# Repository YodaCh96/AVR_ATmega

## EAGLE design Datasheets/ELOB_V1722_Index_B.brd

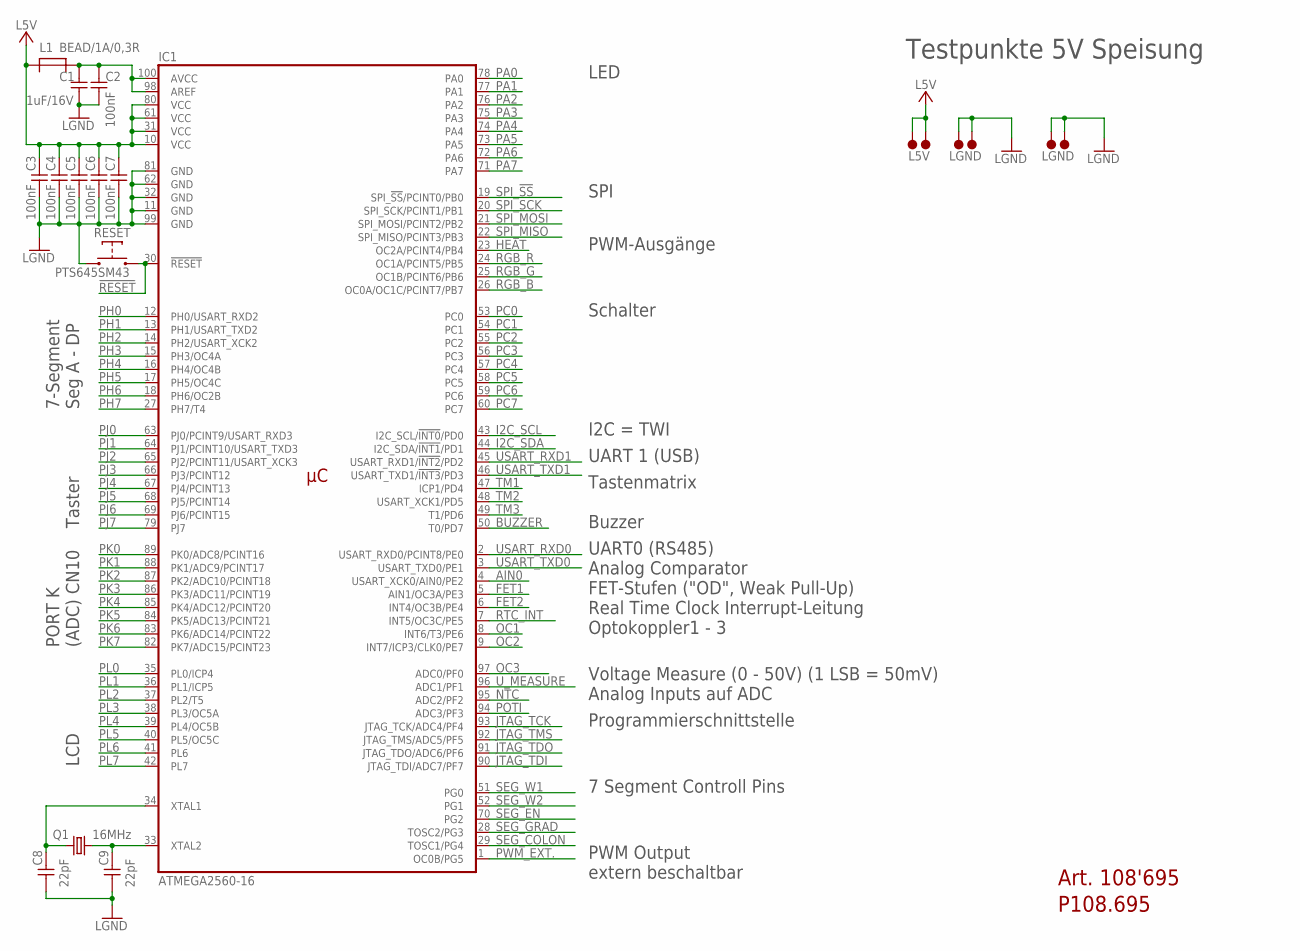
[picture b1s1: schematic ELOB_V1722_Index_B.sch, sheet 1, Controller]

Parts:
.L5V: L5V; TESTPAD_2P_V1_NORESTRICT
C1: 1uF/16V; C0603
C2, C3, C4, C5, C6, C7: 100nF; C0603
C8, C9: 22pF; C0603
IC1: ATMEGA2560-16; TQFP100
L1: BEAD/1A/0,3R; R1206
Q1: 16MHz; HC49_S
RESET: PTS645SM43; DTSM-6
TP1, TP12: LGND; TESTPAD_2P_V1_NORESTRICT

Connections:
!RESET!: IC1.30 (!RESET!), RESET.3 (2), RESET.4 (2); also elsewhere on the board
AIN0: IC1.4 (USART_XCK0/AIN0/PE2); also elsewhere on the board
BUZZER: IC1.50 (T0/PD7); also elsewhere on the board
FET1: IC1.5 (AIN1/OC3A/PE3); also elsewhere on the board
FET2: IC1.6 (INT4/OC3B/PE4); also elsewhere on the board
HEAT: IC1.23 (OC2A/PCINT4/PB4); also elsewhere on the board
I2C_SCL: IC1.43 (I2C_SCL/!INT0!/PD0); also elsewhere on the board
I2C_SDA: IC1.44 (I2C_SDA/!INT1!/PD1); also elsewhere on the board
JTAG_TCK: IC1.93 (JTAG_TCK/ADC4/PF4); also elsewhere on the board
JTAG_TDI: IC1.90 (JTAG_TDI/ADC7/PF7); also elsewhere on the board
JTAG_TDO: IC1.91 (JTAG_TDO/ADC6/PF6); also elsewhere on the board
JTAG_TMS: IC1.92 (JTAG_TMS/ADC5/PF5); also elsewhere on the board
L5V: .L5V.1, .L5V.2, C3.1, C4.1, C5.1, C6.1, C7.1, IC1.10 (VCC), IC1.31 (VCC), IC1.61 (VCC), IC1.80 (VCC), L1.1; also elsewhere on the board
LGND: C1.2, C2.2, C3.2, C4.2, C5.2, C6.2, C7.2, C8.2, C9.2, IC1.11 (GND), IC1.32 (GND), IC1.62 (GND), IC1.81 (GND), IC1.99 (GND), RESET.1, RESET.2 (1), TP1.1, TP1.2, TP12.1, TP12.2; also elsewhere on the board
unnamed: C8.1, IC1.34 (XTAL1), Q1.1
unnamed: C9.1, IC1.33 (XTAL2), Q1.2
unnamed: C1.1, C2.1, IC1.98 (AREF), IC1.100 (AVCC), L1.2
NTC: IC1.95 (ADC2/PF2); also elsewhere on the board
OC1: IC1.8 (INT6/T3/PE6); also elsewhere on the board
OC2: IC1.9 (INT7/ICP3/CLK0/PE7); also elsewhere on the board
OC3: IC1.97 (ADC0/PF0); also elsewhere on the board
PA0: IC1.78 (PA0); also elsewhere on the board
PA1: IC1.77 (PA1); also elsewhere on the board
PA2: IC1.76 (PA2); also elsewhere on the board
PA3: IC1.75 (PA3); also elsewhere on the board
PA4: IC1.74 (PA4); also elsewhere on the board
PA5: IC1.73 (PA5); also elsewhere on the board
PA6: IC1.72 (PA6); also elsewhere on the board
PA7: IC1.71 (PA7); also elsewhere on the board
PC0: IC1.53 (PC0); also elsewhere on the board
PC1: IC1.54 (PC1); also elsewhere on the board
PC2: IC1.55 (PC2); also elsewhere on the board
PC3: IC1.56 (PC3); also elsewhere on the board
PC4: IC1.57 (PC4); also elsewhere on the board
PC5: IC1.58 (PC5); also elsewhere on the board
PC6: IC1.59 (PC6); also elsewhere on the board
PC7: IC1.60 (PC7); also elsewhere on the board
PH0: IC1.12 (PH0/USART_RXD2); also elsewhere on the board
PH1: IC1.13 (PH1/USART_TXD2); also elsewhere on the board
PH2: IC1.14 (PH2/USART_XCK2); also elsewhere on the board
PH3: IC1.15 (PH3/OC4A); also elsewhere on the board
PH4: IC1.16 (PH4/OC4B); also elsewhere on the board
PH5: IC1.17 (PH5/OC4C); also elsewhere on the board
PH6: IC1.18 (PH6/OC2B); also elsewhere on the board
PH7: IC1.27 (PH7/T4); also elsewhere on the board
PJ0: IC1.63 (PJ0/PCINT9/USART_RXD3); also elsewhere on the board
PJ1: IC1.64 (PJ1/PCINT10/USART_TXD3); also elsewhere on the board
PJ2: IC1.65 (PJ2/PCINT11/USART_XCK3); also elsewhere on the board
PJ3: IC1.66 (PJ3/PCINT12); also elsewhere on the board
PJ4: IC1.67 (PJ4/PCINT13); also elsewhere on the board
PJ5: IC1.68 (PJ5/PCINT14); also elsewhere on the board
PJ6: IC1.69 (PJ6/PCINT15); also elsewhere on the board
PJ7: IC1.79 (PJ7); also elsewhere on the board
PK0: IC1.89 (PK0/ADC8/PCINT16); also elsewhere on the board
PK1: IC1.88 (PK1/ADC9/PCINT17); also elsewhere on the board
PK2: IC1.87 (PK2/ADC10/PCINT18); also elsewhere on the board
PK3: IC1.86 (PK3/ADC11/PCINT19); also elsewhere on the board
PK4: IC1.85 (PK4/ADC12/PCINT20); also elsewhere on the board
PK5: IC1.84 (PK5/ADC13/PCINT21); also elsewhere on the board
PK6: IC1.83 (PK6/ADC14/PCINT22); also elsewhere on the board
PK7: IC1.82 (PK7/ADC15/PCINT23); also elsewhere on the board
PL0: IC1.35 (PL0/ICP4); also elsewhere on the board
PL1: IC1.36 (PL1/ICP5); also elsewhere on the board
PL2: IC1.37 (PL2/T5); also elsewhere on the board
PL3: IC1.38 (PL3/OC5A); also elsewhere on the board
PL4: IC1.39 (PL4/OC5B); also elsewhere on the board
PL5: IC1.40 (PL5/OC5C); also elsewhere on the board
PL6: IC1.41 (PL6); also elsewhere on the board
PL7: IC1.42 (PL7); also elsewhere on the board
POTI: IC1.94 (ADC3/PF3); also elsewhere on the board
PWM_EXT.: IC1.1 (OC0B/PG5); also elsewhere on the board
RGB_B: IC1.26 (OC0A/OC1C/PCINT7/PB7); also elsewhere on the board
RGB_G: IC1.25 (OC1B/PCINT6/PB6); also elsewhere on the board
RGB_R: IC1.24 (OC1A/PCINT5/PB5); also elsewhere on the board
RTC_INT: IC1.7 (INT5/OC3C/PE5); also elsewhere on the board
SEG_COLON: IC1.29 (TOSC1/PG4); also elsewhere on the board
SEG_EN: IC1.70 (PG2); also elsewhere on the board
SEG_GRAD: IC1.28 (TOSC2/PG3); also elsewhere on the board
SEG_W1: IC1.51 (PG0); also elsewhere on the board
SEG_W2: IC1.52 (PG1); also elsewhere on the board
SPI_!SS!: IC1.19 (SPI_!SS!/PCINT0/PB0); also elsewhere on the board
SPI_MISO: IC1.22 (SPI_MISO/PCINT3/PB3); also elsewhere on the board
SPI_MOSI: IC1.21 (SPI_MOSI/PCINT2/PB2); also elsewhere on the board
SPI_SCK: IC1.20 (SPI_SCK/PCINT1/PB1); also elsewhere on the board
TM1: IC1.47 (ICP1/PD4); also elsewhere on the board
TM2: IC1.48 (USART_XCK1/PD5); also elsewhere on the board
TM3: IC1.49 (T1/PD6); also elsewhere on the board
USART_RXD0: IC1.2 (USART_RXD0/PCINT8/PE0); also elsewhere on the board
USART_RXD1: IC1.45 (USART_RXD1/!INT2!/PD2); also elsewhere on the board
USART_TXD0: IC1.3 (USART_TXD0/PE1); also elsewhere on the board
USART_TXD1: IC1.46 (USART_TXD1/!INT3!/PD3); also elsewhere on the board
U_MEASURE: IC1.96 (ADC1/PF1); also elsewhere on the board

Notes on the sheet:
7-Segment
PORT K (ADC) CN10
Taster
LCD
Tastenmatrix
Art. 108'695
P108.695
7 Segment Controll Pins
PWM Output
Programmierschnittstelle
Analog Inputs auf ADC
Optokoppler1 - 3
Real Time Clock Interrupt-Leitung
FET-Stufen ("OD", Weak Pull-Up)
Analog Comparator
UART0 (RS485)
UART 1 (USB)
I2C = TWI
Schalter
SPI
LED
PWM-Ausgänge
Seg A - DP
extern beschaltbar
Buzzer
Voltage Measure (0 - 50V) (1 LSB = 50mV)
Testpunkte 5V Speisung

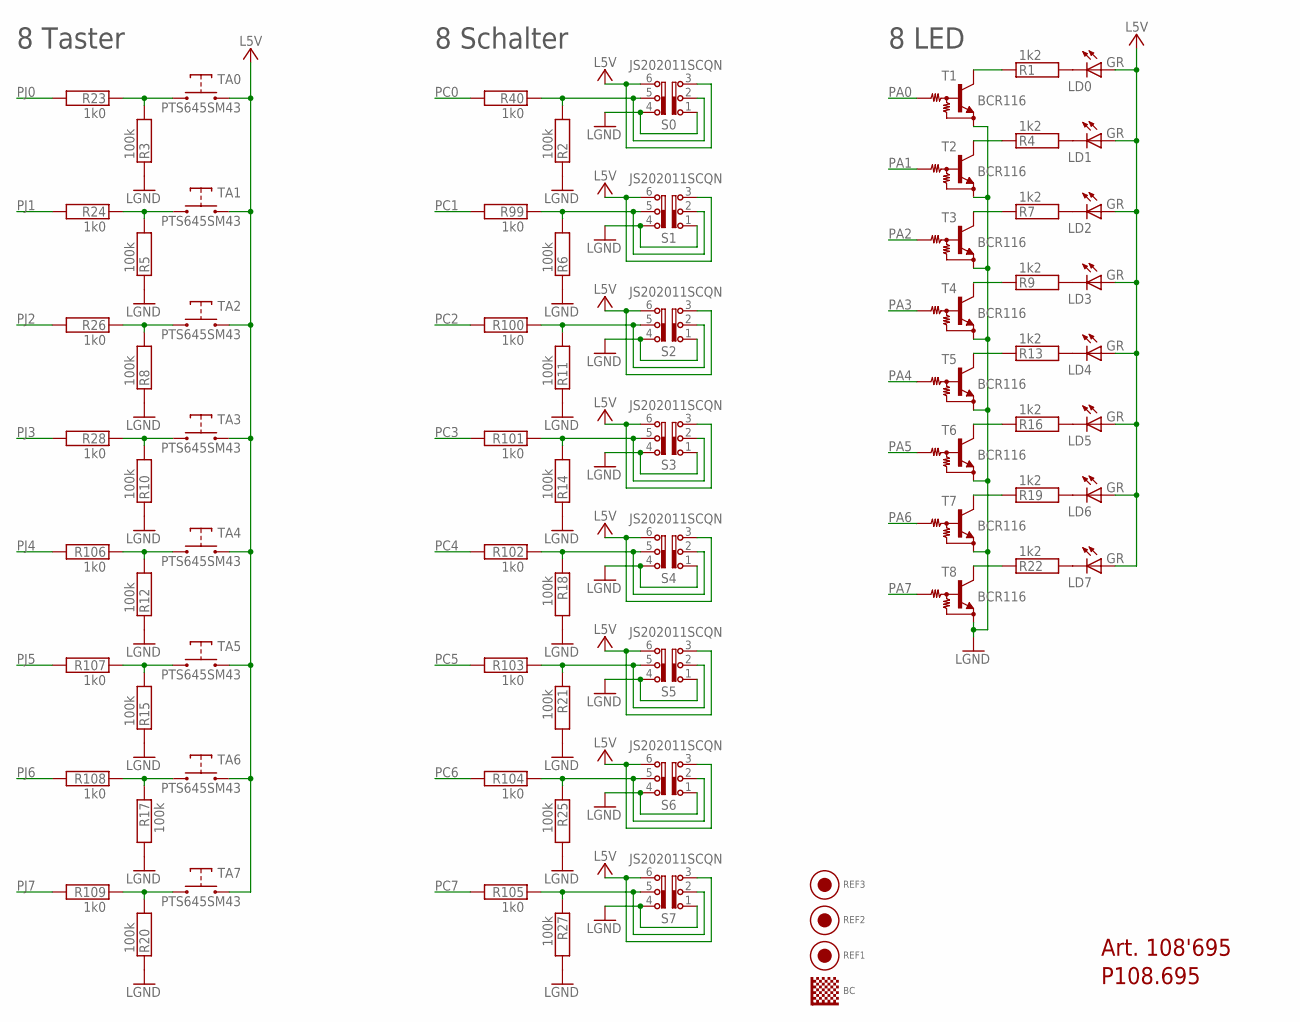
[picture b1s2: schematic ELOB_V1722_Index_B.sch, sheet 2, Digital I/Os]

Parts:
BC: BC; BARCODE
LD0, LD1, LD2, LD3, LD4, LD5, LD6, LD7: GR; LED_0805
R1, R4, R7, R9, R13, R16, R19, R22: 1k2; R0603
R2, R3, R5, R6, R8, R10, R11, R12, R14, R15, R17, R18, R20, R21, R25, R27: 100k; R0603
R23, R24, R26, R28, R40, R99, R100, R101, R102, R103, R104, R105, R106, R107, R108, R109: 1k0; R0603
REF1, REF2, REF3: DOT; PAS_PLACE
S0, S1, S2, S3, S4, S5, S6, S7: JS202011SCQN
T1, T2, T3, T4, T5, T6, T7, T8: BCR116; SOT_23
TA0, TA1, TA2, TA3, TA4, TA5, TA6, TA7: PTS645SM43; DTSM-6

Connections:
L5V: LD0.A, LD1.A, LD2.A, LD3.A, LD4.A, LD5.A, LD6.A, LD7.A, S0.3, S0.6, S1.3, S1.6, S2.3, S2.6, S3.3, S3.6, S4.3, S4.6, S5.3, S5.6, S6.3, S6.6, S7.3, S7.6, TA0.1, TA0.2 (1), TA1.1, TA1.2 (1), TA2.1, TA2.2 (1), TA3.1, TA3.2 (1), TA4.1, TA4.2 (1), TA5.1, TA5.2 (1), TA6.1, TA6.2 (1), TA7.1, TA7.2 (1); also elsewhere on the board
LGND: R2.1, R3.1, R5.1, R6.1, R8.1, R10.1, R11.1, R12.1, R14.1, R15.1, R17.2, R18.2, R20.1, R21.2, R25.2, R27.2, S0.1, S0.4, S1.1, S1.4, S2.1, S2.4, S3.1, S3.4, S4.1, S4.4, S5.1, S5.4, S6.1, S6.4, S7.1, S7.4, T1.2 (E), T2.2 (E), T3.2 (E), T4.2 (E), T5.2 (E), T6.2 (E), T7.2 (E), T8.2 (E); also elsewhere on the board
unnamed: R1.1, T1.3 (C)
unnamed: LD1.K (C), R4.2
unnamed: LD0.K (C), R1.2
unnamed: LD2.K (C), R7.2
unnamed: LD3.K (C), R9.2
unnamed: LD4.K (C), R13.2
unnamed: LD5.K (C), R16.2
unnamed: LD6.K (C), R19.2
unnamed: LD7.K (C), R22.2
unnamed: R4.1, T2.3 (C)
unnamed: R7.1, T3.3 (C)
unnamed: R9.1, T4.3 (C)
unnamed: R13.1, T5.3 (C)
unnamed: R16.1, T6.3 (C)
unnamed: R19.1, T7.3 (C)
unnamed: R22.1, T8.3 (C)
unnamed: R2.2, R40.1, S0.2, S0.5
unnamed: R20.2, R109.1, TA7.3 (2), TA7.4 (2)
unnamed: R27.1, R105.1, S7.2, S7.5
unnamed: R17.1, R108.1, TA6.3 (2), TA6.4 (2)
unnamed: R15.2, R107.1, TA5.3 (2), TA5.4 (2)
unnamed: R12.2, R106.1, TA4.3 (2), TA4.4 (2)
unnamed: R25.1, R104.1, S6.2, S6.5
unnamed: R10.2, R28.1, TA3.3 (2), TA3.4 (2)
unnamed: R6.2, R99.1, S1.2, S1.5
unnamed: R8.2, R26.1, TA2.3 (2), TA2.4 (2)
unnamed: R21.1, R103.1, S5.2, S5.5
unnamed: R18.1, R102.1, S4.2, S4.5
unnamed: R14.2, R101.1, S3.2, S3.5
unnamed: R11.2, R100.1, S2.2, S2.5
unnamed: R5.2, R24.1, TA1.3 (2), TA1.4 (2)
unnamed: R3.2, R23.1, TA0.3 (2), TA0.4 (2)
PA0: T1.1 (B); also elsewhere on the board
PA1: T2.1 (B); also elsewhere on the board
PA2: T3.1 (B); also elsewhere on the board
PA3: T4.1 (B); also elsewhere on the board
PA4: T5.1 (B); also elsewhere on the board
PA5: T6.1 (B); also elsewhere on the board
PA6: T7.1 (B); also elsewhere on the board
PA7: T8.1 (B); also elsewhere on the board
PC0: R40.2; also elsewhere on the board
PC1: R99.2; also elsewhere on the board
PC2: R100.2; also elsewhere on the board
PC3: R101.2; also elsewhere on the board
PC4: R102.2; also elsewhere on the board
PC5: R103.2; also elsewhere on the board
PC6: R104.2; also elsewhere on the board
PC7: R105.2; also elsewhere on the board
PJ0: R23.2; also elsewhere on the board
PJ1: R24.2; also elsewhere on the board
PJ2: R26.2; also elsewhere on the board
PJ3: R28.2; also elsewhere on the board
PJ4: R106.2; also elsewhere on the board
PJ5: R107.2; also elsewhere on the board
PJ6: R108.2; also elsewhere on the board
PJ7: R109.2; also elsewhere on the board

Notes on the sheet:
Art. 108'695
P108.695
8 Taster
8 Schalter
8 LED

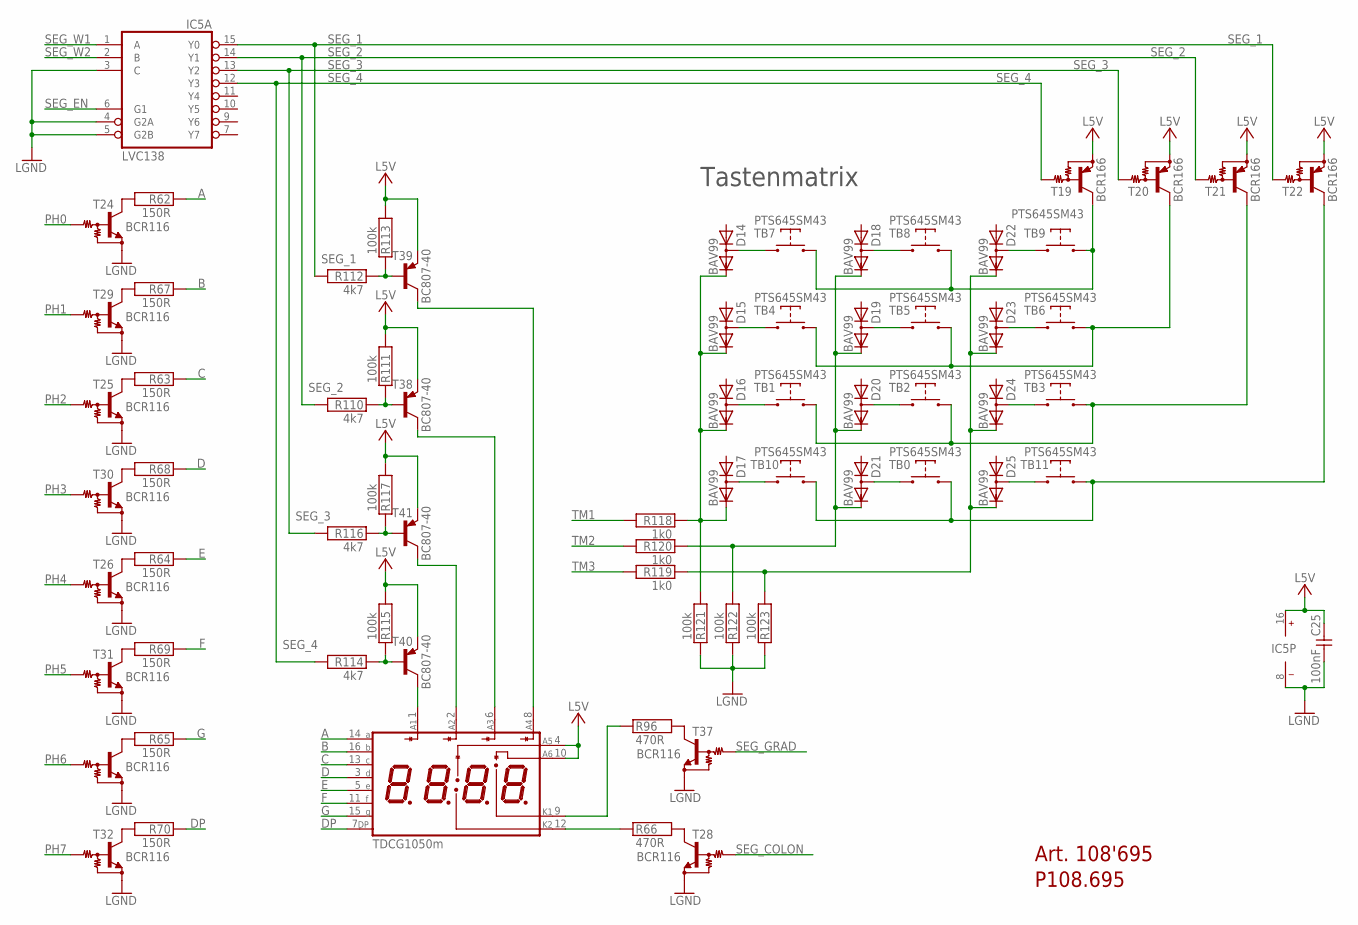
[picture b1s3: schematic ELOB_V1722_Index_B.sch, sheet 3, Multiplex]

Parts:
C25: 100nF; C0603
D14, D15, D16, D17, D18, D19, D20, D21, D22, D23, D24, D25: BAV99; SOT_23
IC5: LVC138; TSSOP_16
R62, R63, R64, R65, R67, R68, R69, R70: 150R; R0603
R66, R96: 470R; R0603
R110, R112, R114, R116: 4k7; R0603
R111, R113, R115, R117, R121, R122, R123: 100k; R0603
R118, R119, R120: 1k0; R0603
SEG1: TDCG1050m; 4-FACH_7-SEGMENT
T19, T20, T21, T22: BCR166; SOT_23
T24, T25, T26, T27, T28, T29, T30, T31, T32, T37: BCR116; SOT_23
T38, T39, T40, T41: BC807-40; SOT23
TB0, TB1, TB2, TB3, TB4, TB5, TB6, TB7, TB8, TB9, TB10, TB11: PTS645SM43; DTSM-6

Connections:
A: R62.1, SEG1.14 (A)
B: R67.1, SEG1.16 (B)
C: R63.1, SEG1.13 (C)
D: R68.1, SEG1.3 (D)
DP: R70.1, SEG1.7 (DP)
E: R64.1, SEG1.5 (E)
F: R69.1, SEG1.11 (F)
G: R65.1, SEG1.15 (G)
L5V: C25.1, IC5.16 (VCC), R111.2, R113.2, R115.2, R117.2, SEG1.4 (A), SEG1.10 (A), T19.2 (E), T20.2 (E), T21.2 (E), T22.2 (E), T38.2 (E), T39.2 (E), T40.2 (E), T41.2 (E); also elsewhere on the board
LGND: C25.2, IC5.3 (C), IC5.4 (G2A), IC5.5 (G2B), IC5.8 (GND), R121.1, R122.1, R123.1, T24.2 (E), T25.2 (E), T26.2 (E), T27.2 (E), T28.2 (E), T29.2 (E), T30.2 (E), T31.2 (E), T32.2 (E), T37.2 (E); also elsewhere on the board
unnamed: T19.3 (C), TB7.3 (2), TB7.4 (2), TB8.3 (2), TB8.4 (2), TB9.3 (2), TB9.4 (2)
unnamed: R66.2, T28.3 (C)
unnamed: R66.1, SEG1.12 (K2)
unnamed: R62.2, T24.3 (C)
unnamed: R67.2, T29.3 (C)
unnamed: T22.3 (C), TB0.3 (2), TB0.4 (2), TB10.3 (2), TB10.4 (2), TB11.3 (2), TB11.4 (2)
unnamed: T21.3 (C), TB1.3 (2), TB1.4 (2), TB2.3 (2), TB2.4 (2), TB3.3 (2), TB3.4 (2)
unnamed: D14.3 (AC), TB7.1, TB7.2 (1)
unnamed: R63.2, T25.3 (C)
unnamed: R68.2, T30.3 (C)
unnamed: R64.2, T26.3 (C)
unnamed: R69.2, T31.3 (C)
unnamed: R65.2, T27.3 (C)
unnamed: R70.2, T32.3 (C)
unnamed: R96.2, T37.3 (C)
unnamed: R96.1, SEG1.9 (K1)
unnamed: R110.1, R111.1, T38.1 (B)
unnamed: R114.1, R115.1, T40.1 (B)
unnamed: R112.1, R113.1, T39.1 (B)
unnamed: R116.1, R117.1, T41.1 (B)
unnamed: SEG1.1 (A), T40.3 (C)
unnamed: SEG1.2 (A), T41.3 (C)
unnamed: SEG1.6 (A), T38.3 (C)
unnamed: SEG1.8 (A), T39.3 (C)
unnamed: D15.3 (AC), TB4.1, TB4.2 (1)
unnamed: T20.3 (C), TB4.3 (2), TB4.4 (2), TB5.3 (2), TB5.4 (2), TB6.3 (2), TB6.4 (2)
unnamed: D16.3 (AC), TB1.1, TB1.2 (1)
unnamed: D17.3 (AC), TB10.1, TB10.2 (1)
unnamed: D22.2 (C), D23.2 (C), D24.2 (C), D25.2 (C), R119.1, R123.2
unnamed: D25.3 (AC), TB11.1, TB11.2 (1)
unnamed: D14.2 (C), D15.2 (C), D16.2 (C), D17.2 (C), R118.1, R121.2
unnamed: D18.3 (AC), TB8.1, TB8.2 (1)
unnamed: D19.3 (AC), TB5.1, TB5.2 (1)
unnamed: D20.3 (AC), TB2.1, TB2.2 (1)
unnamed: D21.3 (AC), TB0.1, TB0.2 (1)
unnamed: D18.2 (C), D19.2 (C), D20.2 (C), D21.2 (C), R120.1, R122.2
unnamed: D22.3 (AC), TB9.1, TB9.2 (1)
unnamed: D23.3 (AC), TB6.1, TB6.2 (1)
unnamed: D24.3 (AC), TB3.1, TB3.2 (1)
PH0: T24.1 (B); also elsewhere on the board
PH1: T29.1 (B); also elsewhere on the board
PH2: T25.1 (B); also elsewhere on the board
PH3: T30.1 (B); also elsewhere on the board
PH4: T26.1 (B); also elsewhere on the board
PH5: T31.1 (B); also elsewhere on the board
PH6: T27.1 (B); also elsewhere on the board
PH7: T32.1 (B); also elsewhere on the board
SEG_1: IC5.15 (Y0), R112.2, T22.1 (B)
SEG_2: IC5.14 (Y1), R110.2, T21.1 (B)
SEG_3: IC5.13 (Y2), R116.2, T20.1 (B)
SEG_4: IC5.12 (Y3), R114.2, T19.1 (B)
SEG_COLON: T28.1 (B); also elsewhere on the board
SEG_EN: IC5.6 (G1); also elsewhere on the board
SEG_GRAD: T37.1 (B); also elsewhere on the board
SEG_W1: IC5.1 (A); also elsewhere on the board
SEG_W2: IC5.2 (B); also elsewhere on the board
TM1: R118.2; also elsewhere on the board
TM2: R120.2; also elsewhere on the board
TM3: R119.2; also elsewhere on the board

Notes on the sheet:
Art. 108'695
P108.695
Tastenmatrix

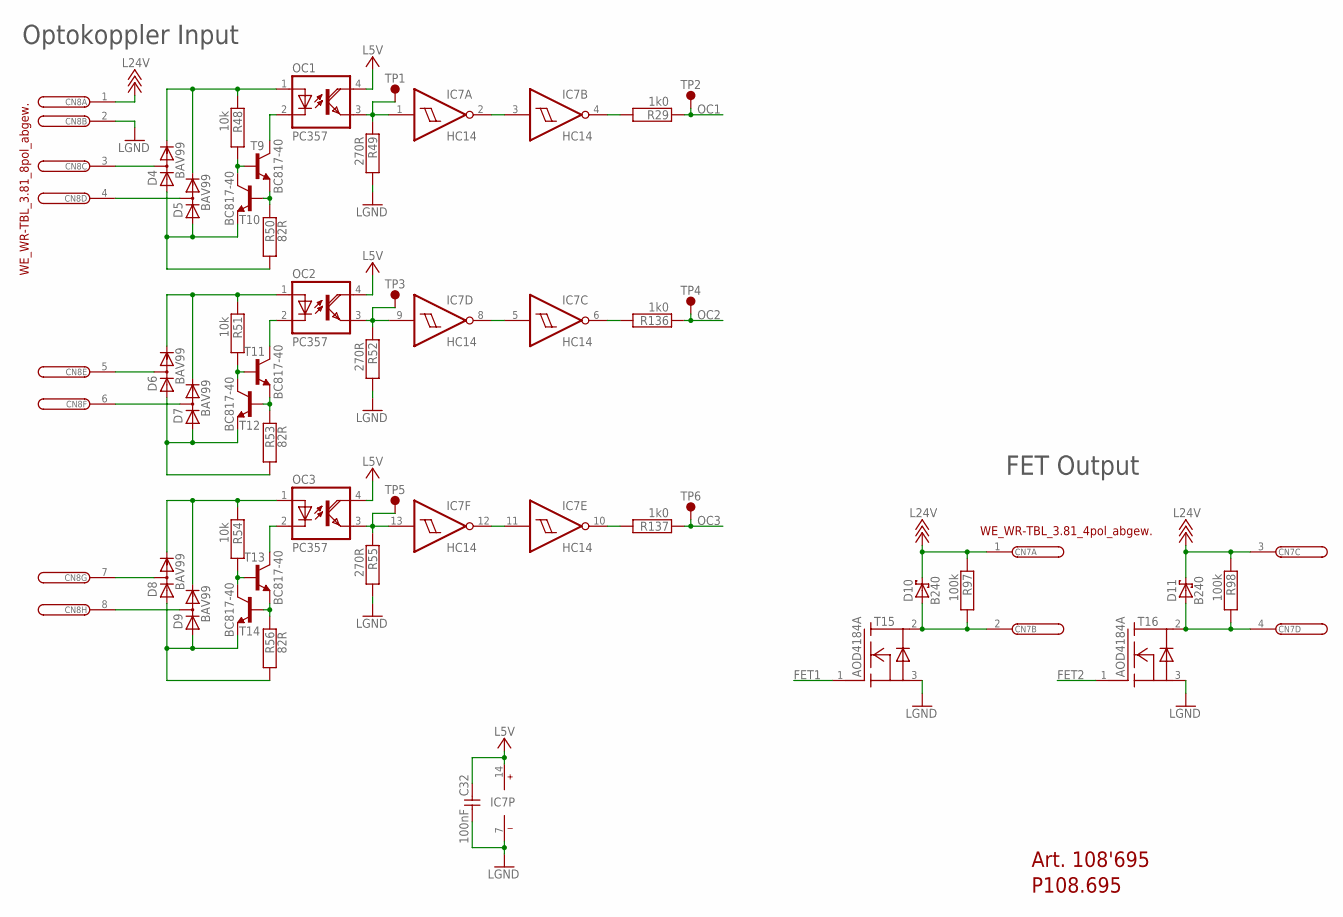
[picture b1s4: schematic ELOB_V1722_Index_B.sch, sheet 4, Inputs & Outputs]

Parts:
C32: 100nF; C0603
CN7: WE_WR-TBL_3.81_4pol_abgew.; PHOENIX_G381_4
CN8: WE_WR-TBL_3.81_8pol_abgew.; PHOENIX_G381_8
D4, D5, D6, D7, D8, D9: BAV99; SOT_23
D10, D11: B240; SMA
IC7: HC14; TSSOP_14
OC1, OC2, OC3: PC357; SOP_4
R29, R136, R137: 1k0; R0603
R48, R51, R54: 10k; R0603
R49, R52, R55: 270R; R0603
R50, R53, R56: 82R; R0603
R97, R98: 100k; R0603
T9, T10, T11, T12, T13, T14: BC817-40; SOT23-BEC
T15, T16: AOD4184A; DPAK
TP4: TP2; ANSCHLUSSPAD_1MM
TP7: TP4; ANSCHLUSSPAD_1MM
TP8: TP6; ANSCHLUSSPAD_1MM
TP9: TP5; ANSCHLUSSPAD_1MM
TP10: TP3; ANSCHLUSSPAD_1MM
TP11: TP1; ANSCHLUSSPAD_1MM

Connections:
FET1: T15.1 (G); also elsewhere on the board
FET2: T16.1 (G); also elsewhere on the board
L5V: C32.1, IC7.14 (VCC), OC1.4 (COL), OC2.4 (COL), OC3.4 (COL); also elsewhere on the board
L24V: CN7.1, CN7.3, CN8.1, D10.C, D11.C, R97.1, R98.1; also elsewhere on the board
LGND: C32.2, CN8.2, IC7.7 (GND), R49.2, R52.2, R55.2, T15.3 (S), T16.3 (S); also elsewhere on the board
unnamed: D4.2 (C), D5.2 (C), OC1.1 (A), R48.1
unnamed: CN8.4, D5.3 (AC)
unnamed: CN8.3, D4.3 (AC)
unnamed: R48.2, T9.1 (B), T10.3 (C)
unnamed: OC1.2 (C), T9.3 (C)
unnamed: R50.1, T9.2 (E), T10.1 (B)
unnamed: D4.1 (A), D5.1 (A), R50.2, T10.2 (E)
unnamed: D6.2 (C), D7.2 (C), OC2.1 (A), R51.1
unnamed: CN8.6, D7.3 (AC)
unnamed: CN8.5, D6.3 (AC)
unnamed: R51.2, T11.1 (B), T12.3 (C)
unnamed: OC2.2 (C), T11.3 (C)
unnamed: R53.1, T11.2 (E), T12.1 (B)
unnamed: D6.1 (A), D7.1 (A), R53.2, T12.2 (E)
unnamed: D8.2 (C), D9.2 (C), OC3.1 (A), R54.1
unnamed: CN8.8, D9.3 (AC)
unnamed: CN8.7, D8.3 (AC)
unnamed: R54.2, T13.1 (B), T14.3 (C)
unnamed: OC3.2 (C), T13.3 (C)
unnamed: R56.1, T13.2 (E), T14.1 (B)
unnamed: D8.1 (A), D9.1 (A), R56.2, T14.2 (E)
unnamed: CN7.2, D10.A, R97.2, T15.2 (D)
unnamed: CN7.4, D11.A, R98.2, T16.2 (D)
unnamed: IC7.5 (I), IC7.8 (O)
unnamed: IC7.11 (I), IC7.12 (O)
unnamed: IC7.2 (O), IC7.3 (I)
unnamed: IC7.13 (I), OC3.3 (EMI), R55.1, TP9.1
unnamed: IC7.9 (I), OC2.3 (EMI), R52.1, TP10.1
unnamed: IC7.1 (I), OC1.3 (EMI), R49.1, TP11.1
unnamed: IC7.10 (O), R137.2
unnamed: IC7.6 (O), R136.2
unnamed: IC7.4 (O), R29.2
OC1: R29.1, TP4.1; also elsewhere on the board
OC2: R136.1, TP7.1; also elsewhere on the board
OC3: R137.1, TP8.1; also elsewhere on the board

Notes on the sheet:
FET Output
Optokoppler Input
Art. 108'695
P108.695

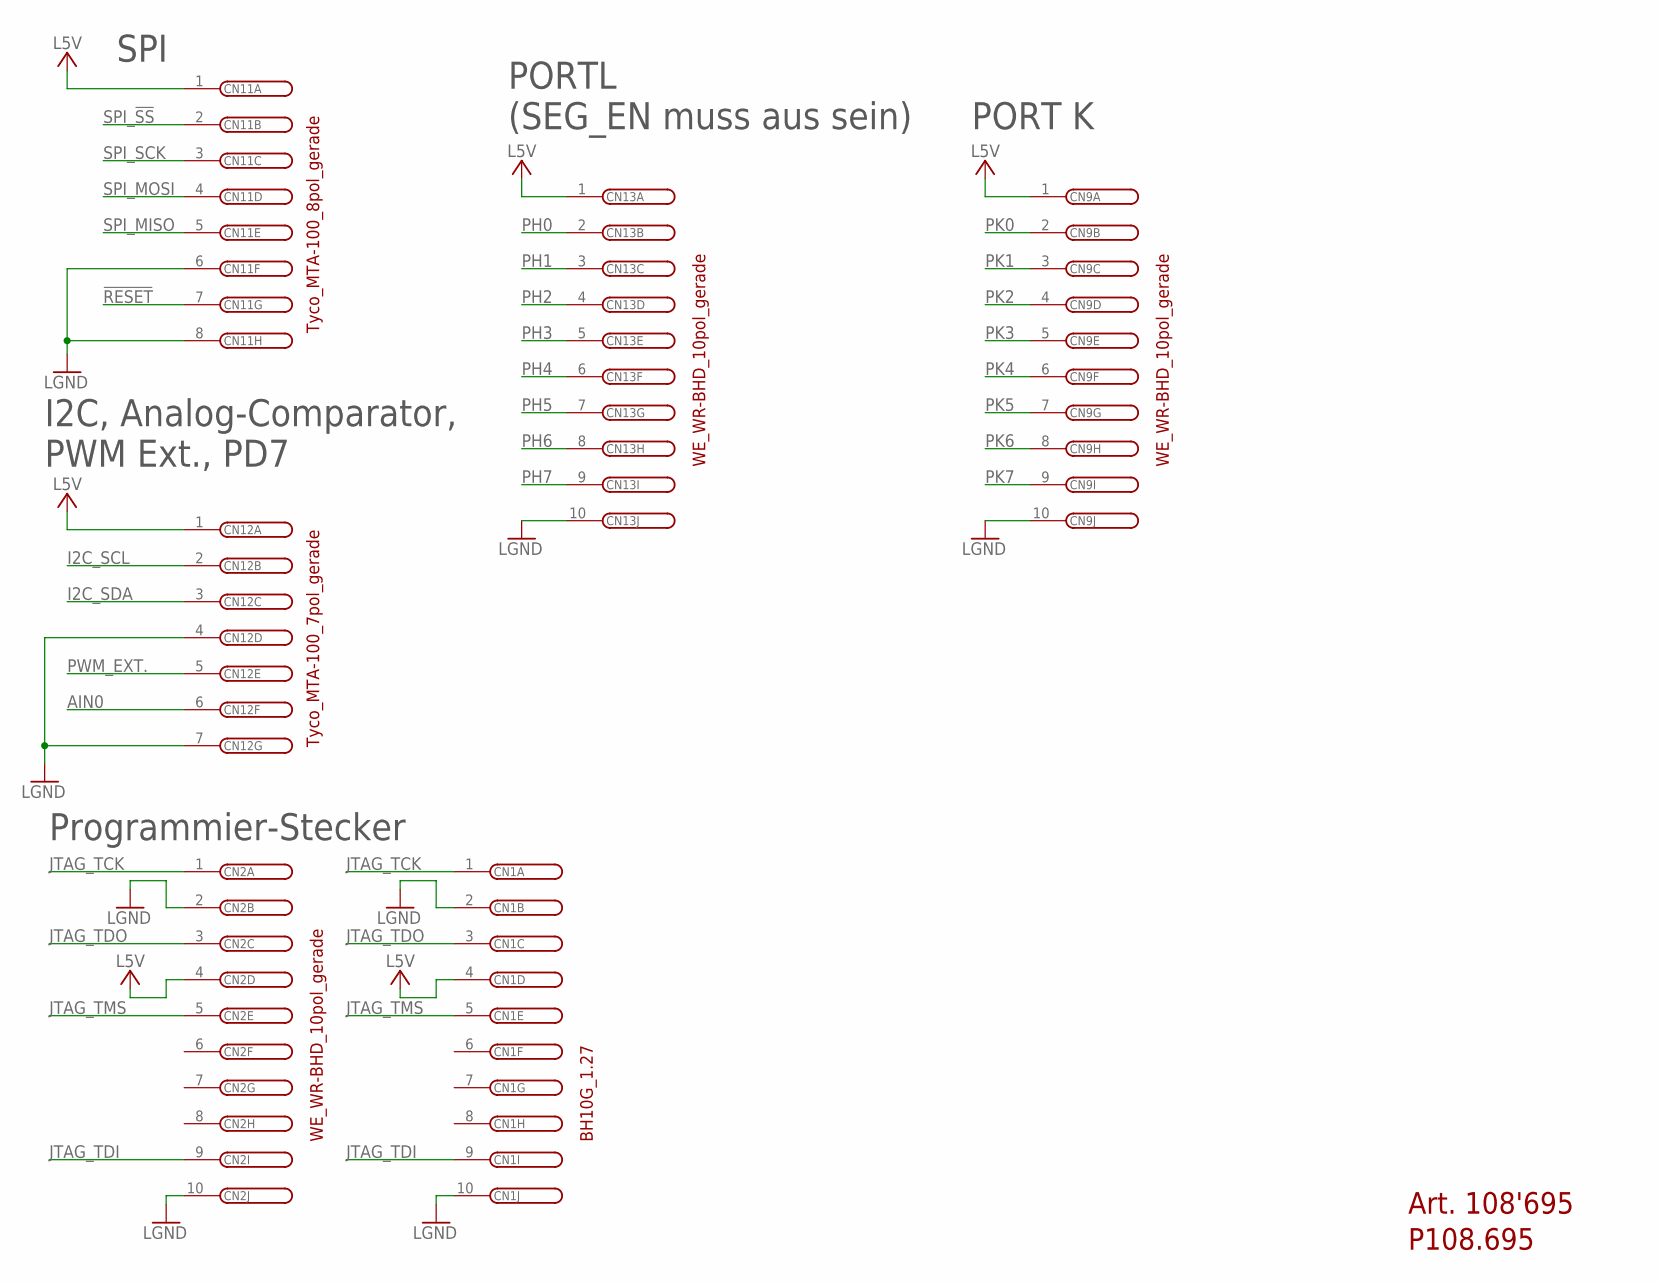
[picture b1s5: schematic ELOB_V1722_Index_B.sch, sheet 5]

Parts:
CN1: BH10G_1.27
CN2, CN9, CN13: WE_WR-BHD_10pol_gerade; BH_10G
CN11: Tyco_MTA-100_8pol_gerade; TYCO_MTA-100_8G
CN12: Tyco_MTA-100_7pol_gerade; TYCO_MTA-100_7G

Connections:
!RESET!: CN11.7; also elsewhere on the board
AIN0: CN12.6; also elsewhere on the board
I2C_SCL: CN12.2; also elsewhere on the board
I2C_SDA: CN12.3; also elsewhere on the board
JTAG_TCK: CN1.1, CN2.1; also elsewhere on the board
JTAG_TDI: CN1.9, CN2.9; also elsewhere on the board
JTAG_TDO: CN1.3, CN2.3; also elsewhere on the board
JTAG_TMS: CN1.5, CN2.5; also elsewhere on the board
L5V: CN1.4, CN2.4, CN9.1, CN11.1, CN12.1, CN13.1; also elsewhere on the board
LGND: CN1.2, CN1.10, CN2.2, CN2.10, CN9.10, CN11.6, CN11.8, CN12.4, CN12.7, CN13.10; also elsewhere on the board
PH0: CN13.2; also elsewhere on the board
PH1: CN13.3; also elsewhere on the board
PH2: CN13.4; also elsewhere on the board
PH3: CN13.5; also elsewhere on the board
PH4: CN13.6; also elsewhere on the board
PH5: CN13.7; also elsewhere on the board
PH6: CN13.8; also elsewhere on the board
PH7: CN13.9; also elsewhere on the board
PK0: CN9.2; also elsewhere on the board
PK1: CN9.3; also elsewhere on the board
PK2: CN9.4; also elsewhere on the board
PK3: CN9.5; also elsewhere on the board
PK4: CN9.6; also elsewhere on the board
PK5: CN9.7; also elsewhere on the board
PK6: CN9.8; also elsewhere on the board
PK7: CN9.9; also elsewhere on the board
PWM_EXT.: CN12.5; also elsewhere on the board
SPI_!SS!: CN11.2; also elsewhere on the board
SPI_MISO: CN11.5; also elsewhere on the board
SPI_MOSI: CN11.4; also elsewhere on the board
SPI_SCK: CN11.3; also elsewhere on the board

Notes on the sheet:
Art. 108'695
P108.695
Programmier-Stecker
PORT K
SPI
I2C, Analog-Comparator, PWM Ext., PD7
PORTL (SEG_EN muss aus sein)

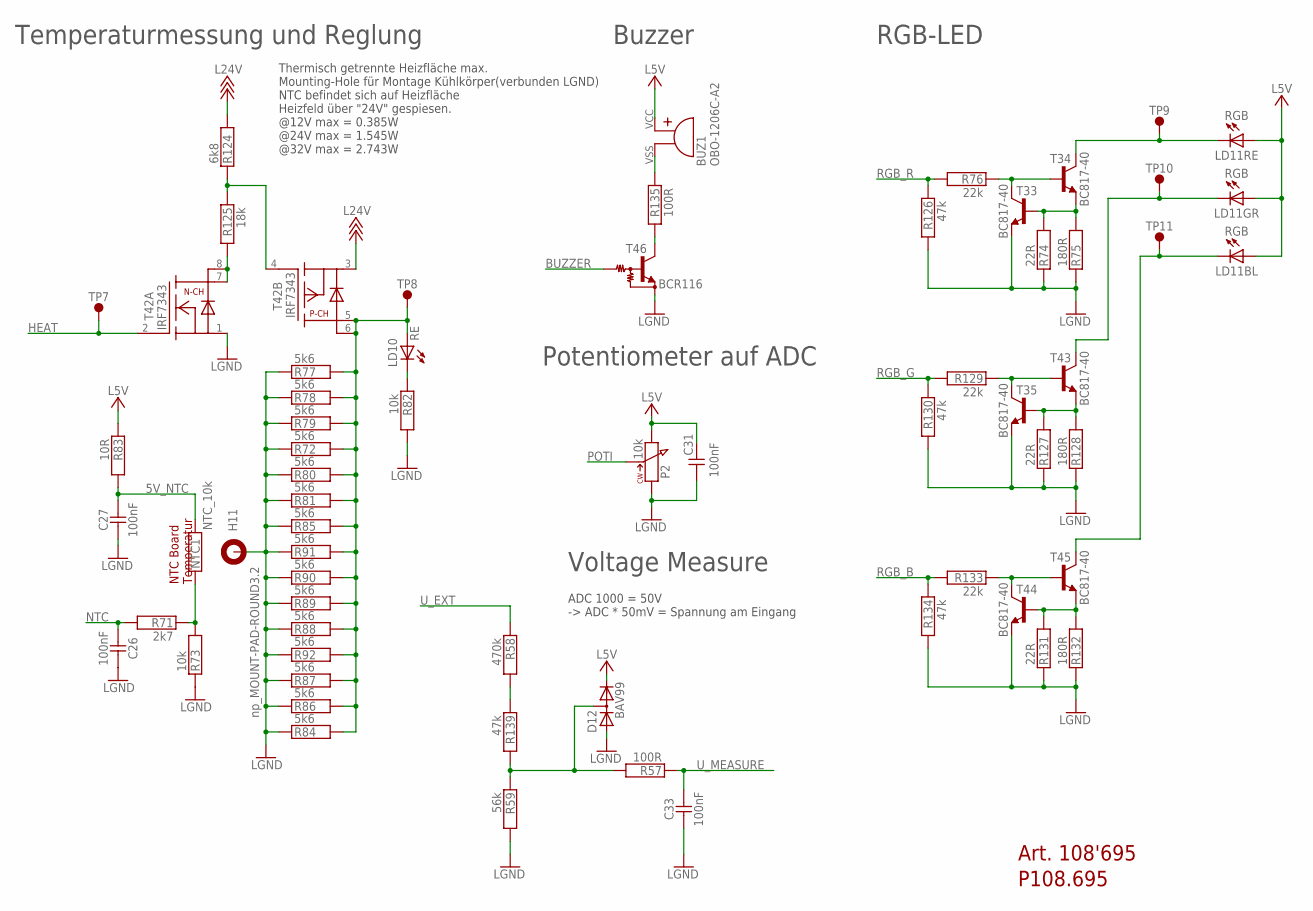
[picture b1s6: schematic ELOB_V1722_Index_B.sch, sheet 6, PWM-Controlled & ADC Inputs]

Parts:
BUZ1: OBO-1206C-A2; BUZ_TCW12
C26, C27, C31, C33: 100nF; C0603
D12: BAV99; SOT_23
H11: np_MOUNT-PAD-ROUND3.2; 3,2-PAD
LD10: RE; LED_0805
LD11: RGB; LED_HARVATEK_HT-U3A8
NTC1: NTC_10k; R1206
P2: 10k; POTI_PIHER_PTC-15
R57: 100R; R0603
R58: 470k; R1206
R59: 56k; R1206
R71: 2k7; R0603
R72, R77, R78, R79, R80, R81, R84, R85, R86, R87, R88, R89, R90, R91, R92: 5k6; R1206
R73, R82: 10k; R0603
R74, R127, R131: 22R; R0603
R75, R128, R132: 180R; R0603
R76, R129, R133: 22k; R0603
R83: 10R; R0603
R124: 6k8; R0603
R125: 18k; R0603
R126, R130, R134: 47k; R0603
R135: 100R; R1206
R139: 47k; R1206
T33, T34, T35, T43, T44, T45: BC817-40; SOT23-BEC
T42: IRF7343; SO-8_FET
T46: BCR116; SOT_23
TP2: TP8; ANSCHLUSSPAD_1MM
TP3: TP10; ANSCHLUSSPAD_1MM
TP5: TP9; ANSCHLUSSPAD_1MM
TP6: TP11; ANSCHLUSSPAD_1MM
TP13: TP7; ANSCHLUSSPAD_1MM

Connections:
5V_NTC: C27.1, NTC1.2, R83.2
BUZZER: T46.1 (B); also elsewhere on the board
HEAT: T42.2 (G), TP13.1; also elsewhere on the board
L5V: BUZ1.VCC (+), C31.1, D12.2 (C), LD11.1 (A), LD11.2 (A), LD11.3 (A), P2.E (2), R83.1; also elsewhere on the board
L24V: R124.2, T42.3 (S); also elsewhere on the board
LGND: C26.2, C27.2, C31.2, C33.2, D12.1 (A), H11.B3,2, P2.A (1), R59.2, R72.1, R73.1, R74.1, R75.1, R77.1, R78.1, R79.1, R80.1, R81.1, R82.2, R84.1, R85.1, R86.1, R87.1, R88.1, R89.1, R90.1, R91.1, R92.1, R126.2, R127.1, R128.1, R130.2, R131.1, R132.1, R134.2, T33.2 (E), T35.2 (E), T42.1 (S), T44.2 (E), T46.2 (E); also elsewhere on the board
unnamed: R58.2, R139.1
unnamed: R76.1, T33.3 (C), T34.1 (B)
unnamed: R74.2, R75.2, T33.1 (B), T34.2 (E)
unnamed: R129.1, T35.3 (C), T43.1 (B)
unnamed: R127.2, R128.2, T35.1 (B), T43.2 (E)
unnamed: R133.1, T44.3 (C), T45.1 (B)
unnamed: R131.2, R132.2, T44.1 (B), T45.2 (E)
unnamed: NTC1.1, R71.1, R73.2
unnamed: D12.3 (AC), R57.2, R59.1, R139.2
unnamed: LD10.K (C), R82.1
unnamed: LD10.A, R72.2, R77.2, R78.2, R79.2, R80.2, R81.2, R84.2, R85.2, R86.2, R87.2, R88.2, R89.2, R90.2, R91.2, R92.2, T42.5 (D1), T42.6 (D2), TP2.1
unnamed: R125.2, T42.7 (D1), T42.8 (D2)
unnamed: R124.1, R125.1, T42.4 (G)
unnamed: LD11.4 (C), T45.3 (C), TP6.1
unnamed: LD11.5 (C), T43.3 (C), TP3.1
unnamed: LD11.6 (C), T34.3 (C), TP5.1
unnamed: BUZ1.VSS (-), R135.1
unnamed: R135.2, T46.3 (C)
NTC: C26.1, R71.2; also elsewhere on the board
POTI: P2.S; also elsewhere on the board
RGB_B: R133.2, R134.1; also elsewhere on the board
RGB_G: R129.2, R130.1; also elsewhere on the board
RGB_R: R76.2, R126.1; also elsewhere on the board
U_EXT: R58.1; also elsewhere on the board
U_MEASURE: C33.1, R57.1; also elsewhere on the board

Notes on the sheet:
Thermisch getrennte Heizfläche max. Mounting-Hole für Montage Kühlkörper(verbunden LGND) NTC befindet sich auf Heizfläche Heizfeld über "24V" gespiesen. @12V max = 0.385W @24V max = 1.545W @32V max = 2.743W
RGB-LED
Potentiometer auf ADC
Temperaturmessung und Reglung
NTC Board Temperatur
Art. 108'695
P108.695
Buzzer
Voltage Measure
ADC 1000 = 50V -> ADC * 50mV = Spannung am Eingang

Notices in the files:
elob_os/elob_base.h:
@copyright (C) 2018 Pius Steiner, GNU General Public License Version 3
parts and their libraries:
switch-ck: Copyright (C) 2011, Bob Starr
